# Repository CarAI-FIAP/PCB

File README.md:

# PCB
Placa em PCB para centralizar as conexões. Projeto em KiCAD

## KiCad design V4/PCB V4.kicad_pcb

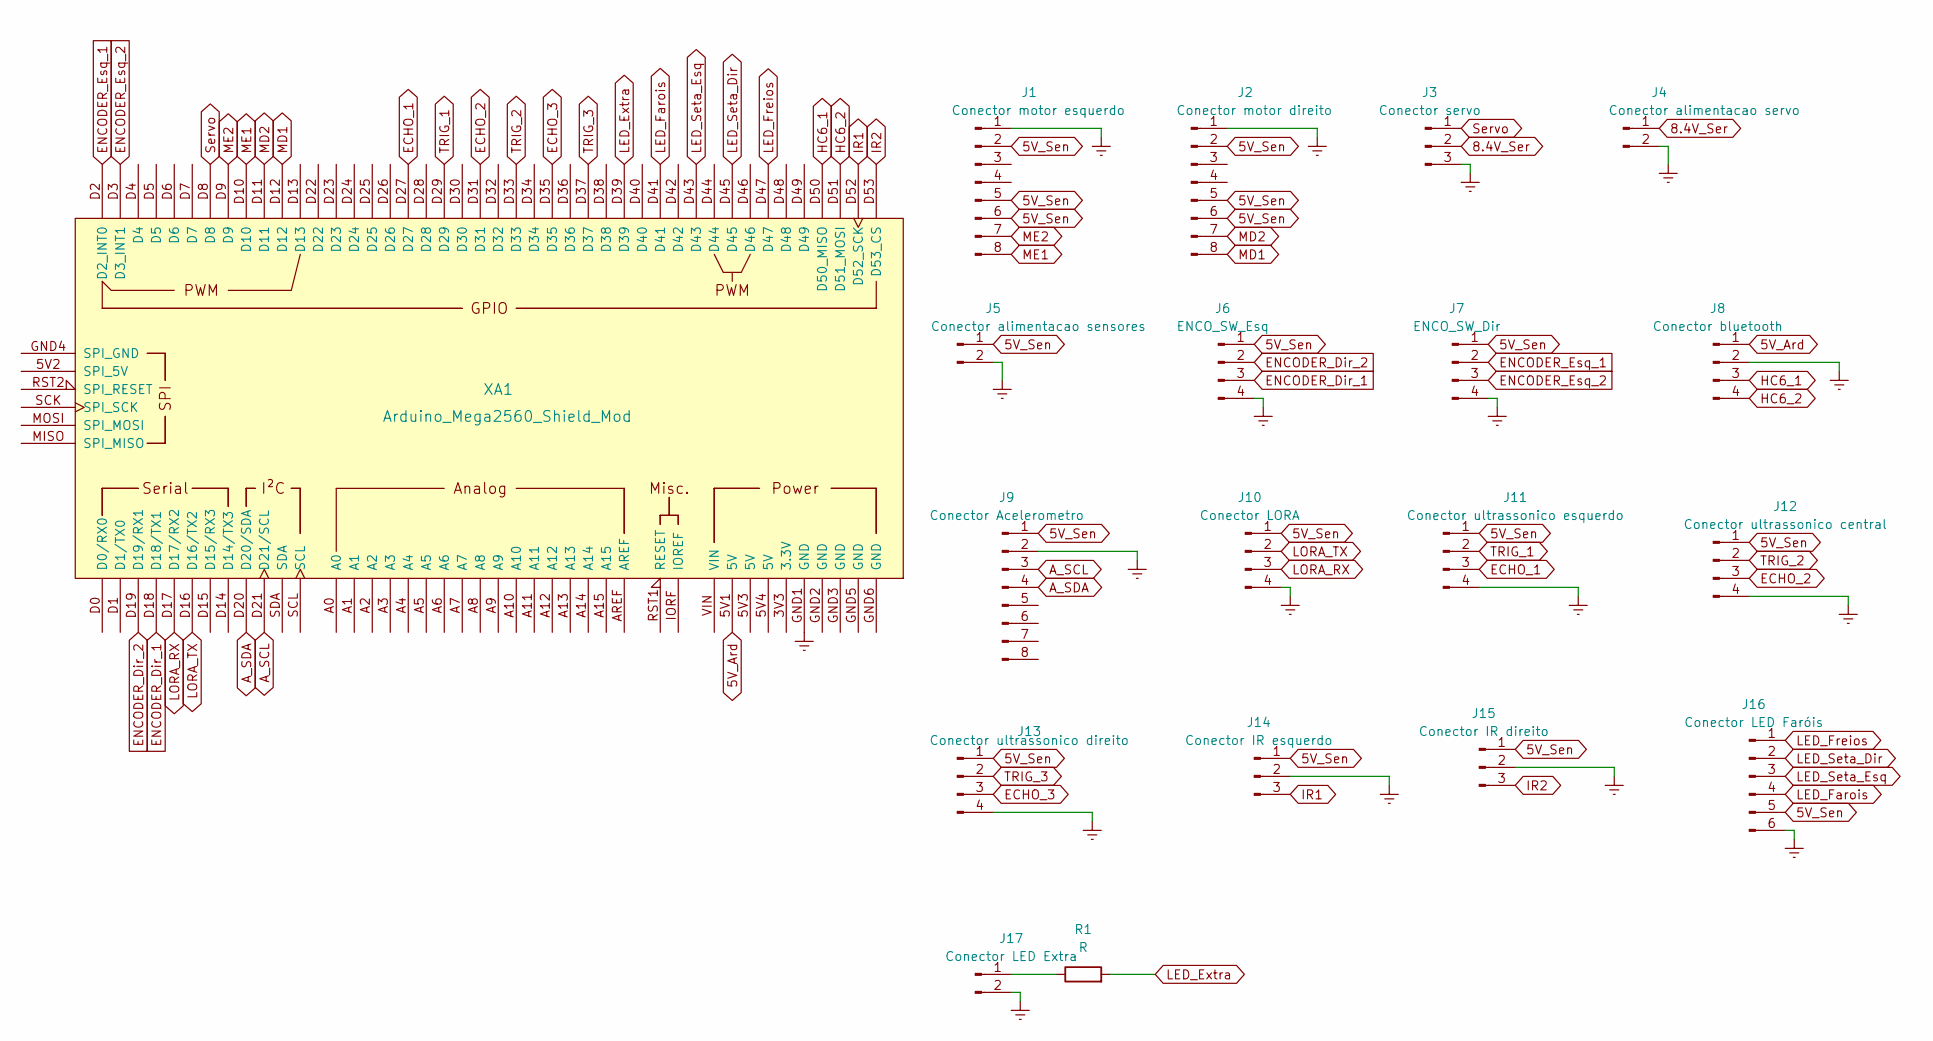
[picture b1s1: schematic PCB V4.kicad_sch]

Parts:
J1: Conector motor esquerdo; PinSocket_2x04_P2.54mm_Vertical
J2: Conector motor direito; PinSocket_2x04_P2.54mm_Vertical
J3: Conector servo; TerminalBlock_Phoenix_MKDS-1,5-3_1x03_P5.00mm_Horizontal
J4: Conector alimentacao servo; TerminalBlock_Phoenix_MKDS-1,5-2_1x02_P5.00mm_Horizontal
J5: Conector alimentacao sensores; TerminalBlock_Phoenix_MKDS-1,5-2_1x02_P5.00mm_Horizontal
J6: ENCO_SW_Esq; TerminalBlock_Phoenix_MKDS-1,5-4_1x04_P5.00mm_Horizontal
J7: ENCO_SW_Dir; TerminalBlock_Phoenix_MKDS-1,5-4_1x04_P5.00mm_Horizontal
J8: Conector bluetooth; PinSocket_1x04_P2.54mm_Vertical
J9: Conector Acelerometro; PinSocket_1x08_P2.54mm_Vertical
J10: Conector LORA; JST_XH_B4B-XH-A_1x04_P2.50mm_Vertical
J11: Conector ultrassonico esquerdo; JST_XH_B4B-XH-A_1x04_P2.50mm_Vertical
J12: Conector ultrassonico central; JST_XH_B4B-XH-A_1x04_P2.50mm_Vertical
J13: Conector ultrassonico direito; JST_XH_B4B-XH-A_1x04_P2.50mm_Vertical
J14: Conector IR esquerdo; JST_XH_B3B-XH-A_1x03_P2.50mm_Vertical
J15: Conector IR direito; JST_XH_B3B-XH-A_1x03_P2.50mm_Vertical
J16: Conector LED Faróis; TerminalBlock_Phoenix_MKDS-1,5-6_1x06_P5.00mm_Horizontal
J17: Conector LED Extra; JST_XH_B2B-XH-A_1x02_P2.50mm_Vertical
R1: R; R_Axial_DIN0207_L6.3mm_D2.5mm_P10.16mm_Horizontal
XA1: Arduino_Mega2560_Shield_Mod; Arduino_Mega2560_R3_Shield_No_Holes

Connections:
5V_Ard: J8.1, XA1.5V1 (5V)
5V_Sen: J1.2, J1.5, J1.6, J2.2, J2.5, J2.6, J5.1, J6.1, J7.1, J9.1, J10.1, J11.1, J12.1, J13.1, J14.1, J15.1, J16.5
8.4V_Ser: J3.2, J4.1
A_SCL: J9.3, XA1.D21 (D21/SCL)
A_SDA: J9.4, XA1.D20 (D20/SDA)
ECHO_1: J11.3, XA1.D27
ECHO_2: J12.3, XA1.D31
ECHO_3: J13.3, XA1.D35
ENCODER_Dir_1: J6.3, XA1.D18 (D18/TX1)
ENCODER_Dir_2: J6.2, XA1.D19 (D19/RX1)
ENCODER_Esq_1: J7.2, XA1.D2 (D2_INT0)
ENCODER_Esq_2: J7.3, XA1.D3 (D3_INT1)
Earth: J1.1, J2.1, J3.3, J4.2, J5.2, J6.4, J7.4, J8.2, J9.2, J10.4, J11.4, J12.4, J13.4, J14.2, J15.2, J16.6, J17.2, XA1.GND1 (GND)
HC6_1: J8.3, XA1.D50 (D50_MISO)
HC6_2: J8.4, XA1.D51 (D51_MOSI)
IR1: J14.3, XA1.D52 (D52_SCK)
IR2: J15.3, XA1.D53 (D53_CS)
LED_Extra: R1.2, XA1.D39
LED_Farois: J16.4, XA1.D41
LED_Freios: J16.1, XA1.D47
LED_Seta_Dir: J16.2, XA1.D45
LED_Seta_Esq: J16.3, XA1.D43
LORA_RX: J10.3, XA1.D17 (D17/RX2)
LORA_TX: J10.2, XA1.D16 (D16/TX2)
MD1: J2.8, XA1.D12
MD2: J2.7, XA1.D11
ME1: J1.8, XA1.D10
ME2: J1.7, XA1.D9
unnamed: J17.1, R1.1
Servo: J3.1, XA1.D8
TRIG_1: J11.2, XA1.D29
TRIG_2: J12.2, XA1.D33
TRIG_3: J13.2, XA1.D37

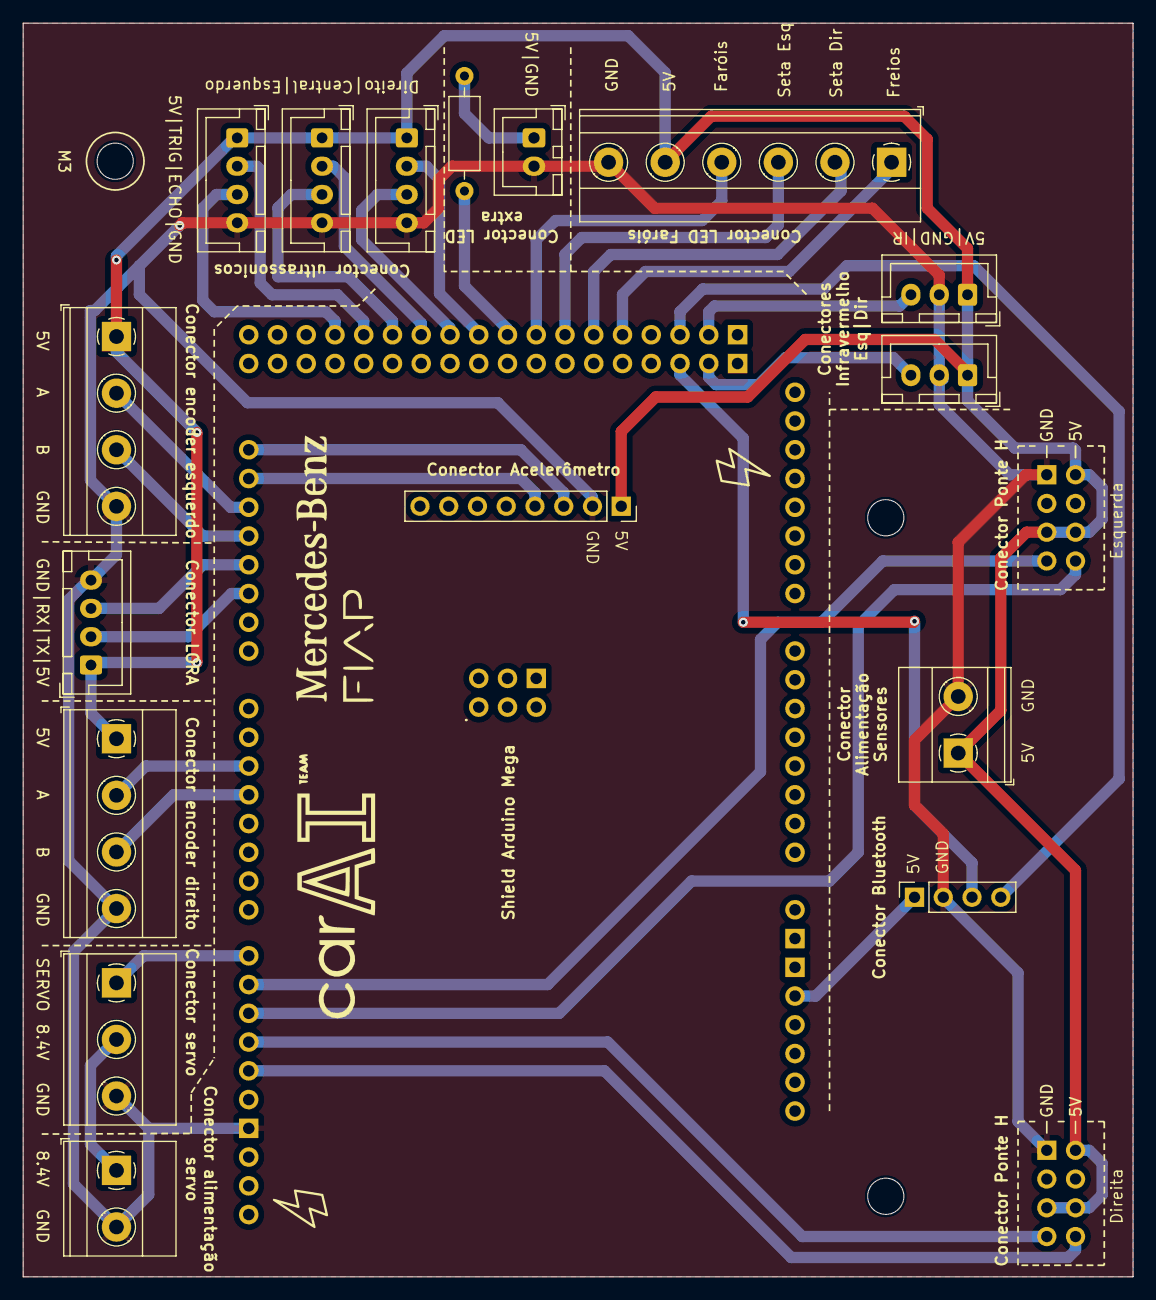
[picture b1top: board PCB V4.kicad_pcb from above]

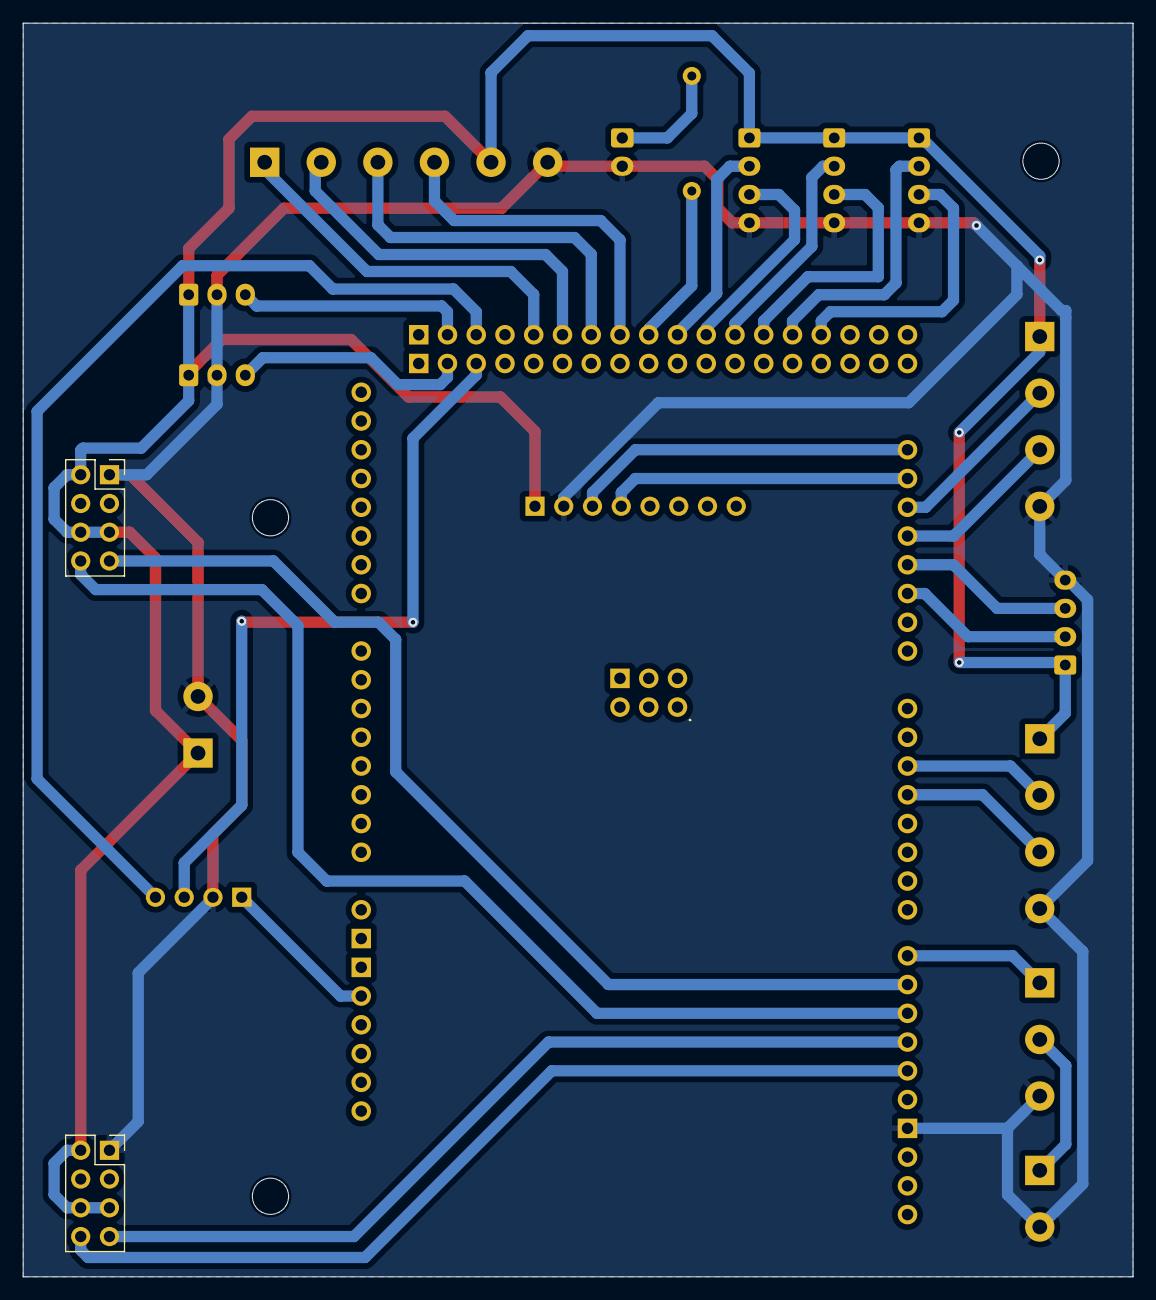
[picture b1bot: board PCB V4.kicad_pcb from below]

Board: 2 copper layers, 98.0 x 110.7 mm, 19 parts (2 on the bottom side), 33 nets.

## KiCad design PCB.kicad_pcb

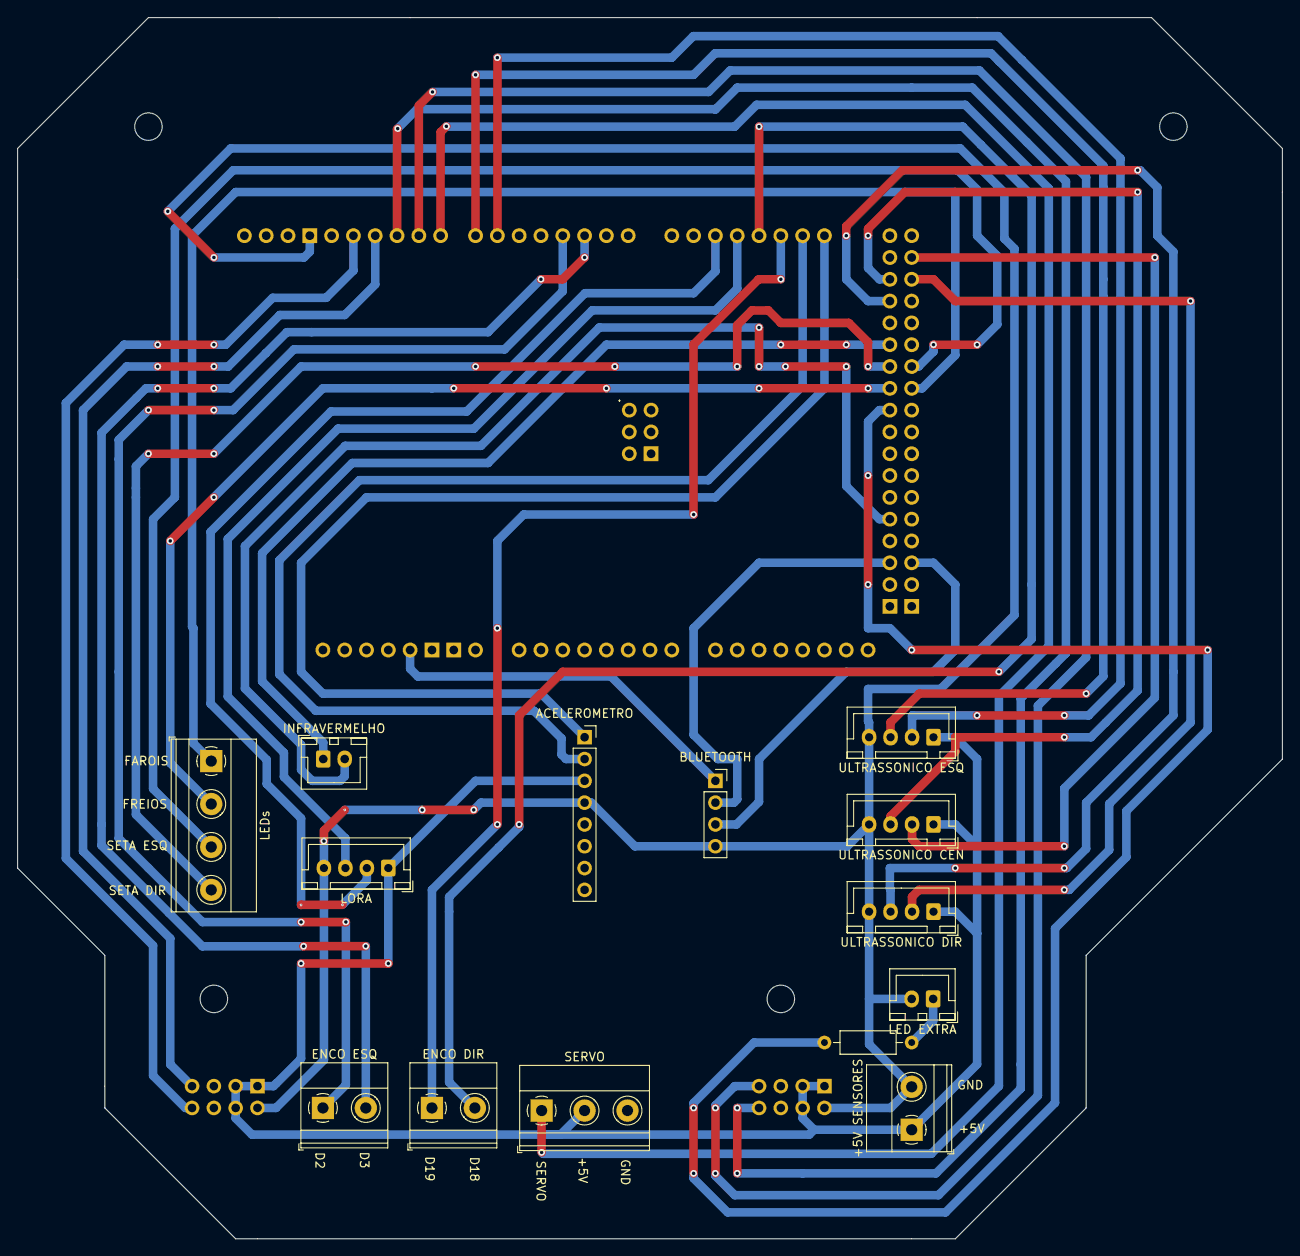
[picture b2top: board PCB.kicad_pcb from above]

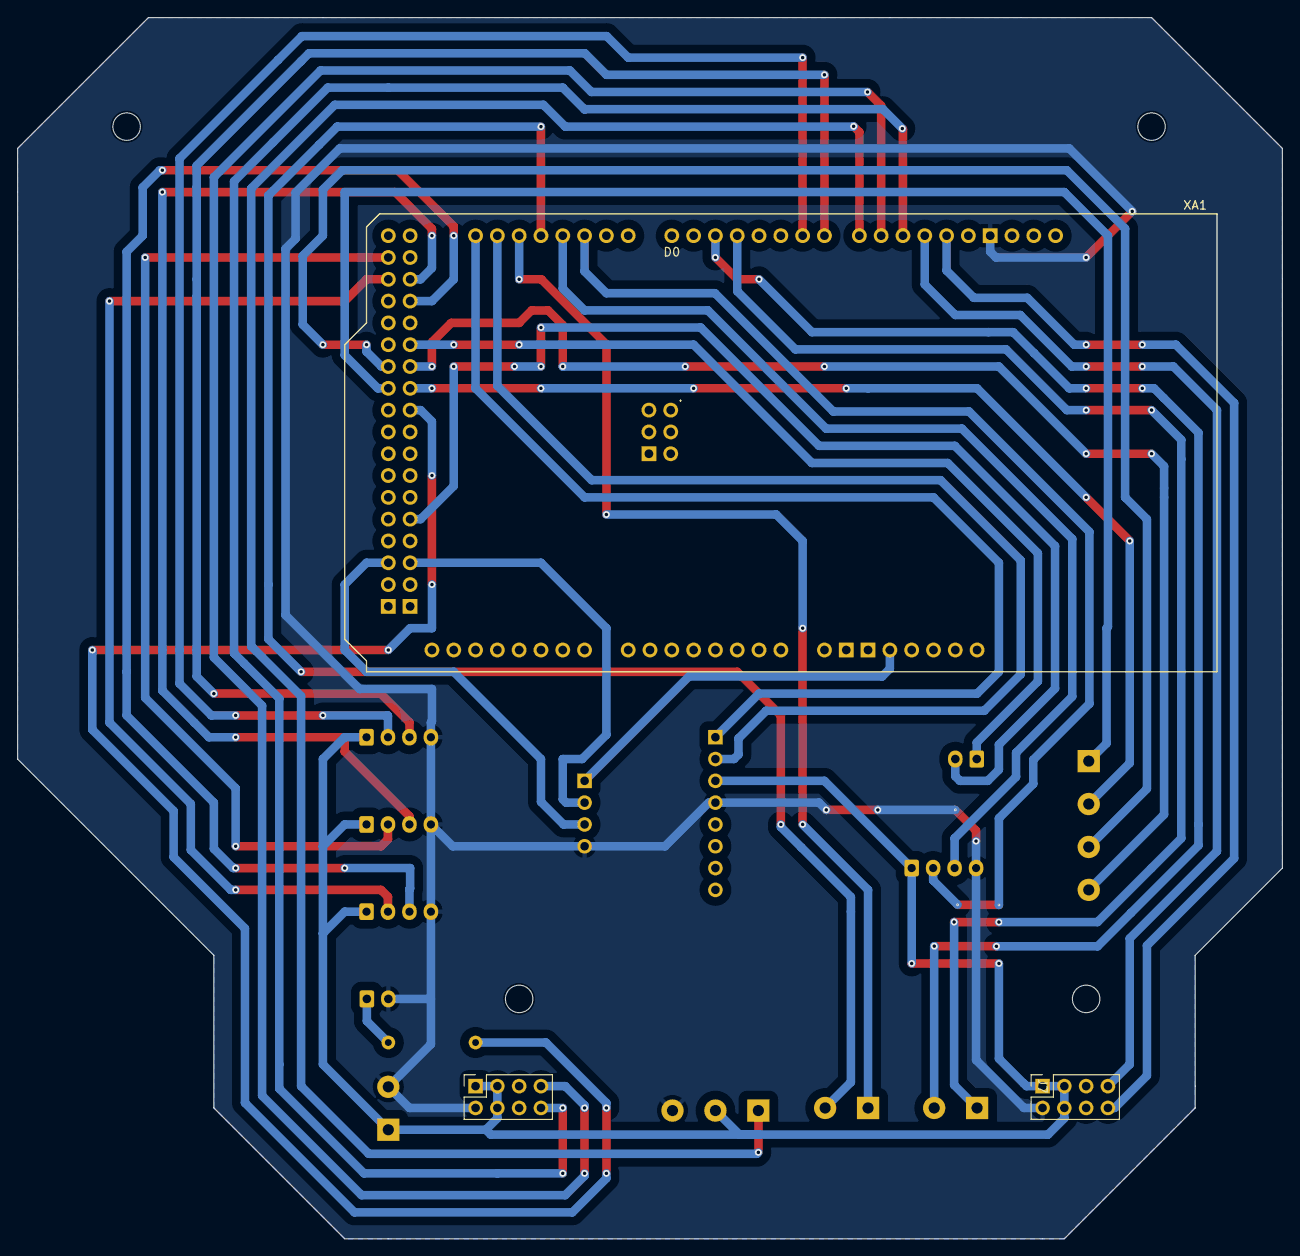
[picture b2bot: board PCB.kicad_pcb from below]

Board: 2 copper layers, 147.3 x 142.2 mm, 17 parts (2 on the bottom side), 32 nets.

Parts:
+5V SENSORES: Conector alimentacao sensores; TerminalBlock_Phoenix_MKDS-1,5-2_1x02_P5.00mm_Horizontal
ACELEROMETRO: Conector Acelerometro; PinSocket_1x08_P2.54mm_Vertical
BLUETOOTH: Conector bluetooth; PinSocket_1x04_P2.54mm_Vertical
ENCO DIR: ENCO_SW_Dir; TerminalBlock_Phoenix_MKDS-1,5-2_1x02_P5.00mm_Horizontal
ENCO ESQ: ENCO_SW_Esq; TerminalBlock_Phoenix_MKDS-1,5-2_1x02_P5.00mm_Horizontal
INFRAVERMELHO: Conector IR; JST_XH_B2B-XH-A_1x02_P2.50mm_Vertical
J7: PONTA H 1; PinSocket_2x04_P2.54mm_Vertical
LED EXTRA: Conector LED Extra; JST_XH_B2B-XH-A_1x02_P2.50mm_Vertical
LEDs: LEDs; TerminalBlock_Phoenix_MKDS-1,5-4_1x04_P5.00mm_Horizontal
LORA: Conector LORA; JST_XH_B4B-XH-A_1x04_P2.50mm_Vertical
PONTE H 2: Conector motor esquerdo; PinSocket_2x04_P2.54mm_Vertical
R1: R; R_Axial_DIN0207_L6.3mm_D2.5mm_P10.16mm_Horizontal
SERVO: Conector servo; TerminalBlock_Phoenix_MKDS-1,5-3_1x03_P5.00mm_Horizontal
ULTRASSONICO CEN: Conector ultrassonico central; JST_XH_B4B-XH-A_1x04_P2.50mm_Vertical
ULTRASSONICO DIR: Conector ultrassonico direito; JST_XH_B4B-XH-A_1x04_P2.50mm_Vertical
ULTRASSONICO ESQ: Conector ultrassonico esquerdo; JST_XH_B4B-XH-A_1x04_P2.50mm_Vertical
XA1: Arduino_Mega2560_Shield_Mod; Arduino_Mega2560_R3_Shield_Sem_furo

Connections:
5V_Ard: BLUETOOTH.1, XA1.5V1 (5V)
5V_Sen: +5V SENSORES.1, ACELEROMETRO.3, J7.1, J7.3, J7.4, LORA.1, PONTE H 2.1, PONTE H 2.3, PONTE H 2.4, SERVO.2, ULTRASSONICO CEN.1, ULTRASSONICO DIR.1, ULTRASSONICO ESQ.1
A_SCL: ACELEROMETRO.1, XA1.D21 (D21/SCL)
A_SDA: ACELEROMETRO.2, XA1.D20 (D20/SDA)
ECHO_1: ULTRASSONICO ESQ.2, XA1.D6
ECHO_2: ULTRASSONICO CEN.2, XA1.D23
ECHO_3: ULTRASSONICO DIR.2, XA1.D25
Earth: +5V SENSORES.2, ACELEROMETRO.4, BLUETOOTH.4, J7.2, LED EXTRA.2, LORA.4, PONTE H 2.2, SERVO.3, ULTRASSONICO CEN.4, ULTRASSONICO DIR.4, ULTRASSONICO ESQ.4, XA1.GND1 (GND)
HC6_1: BLUETOOTH.2, XA1.D50 (D50_MISO)
HC6_2: BLUETOOTH.3, XA1.D51 (D51_MOSI)
IR1: INFRAVERMELHO.1, XA1.D30
IR2: INFRAVERMELHO.2, XA1.D46
LED_Extra: R1.2, XA1.D36
LORA_RX: LORA.3, XA1.D17 (D17/RX2)
LORA_TX: LORA.2, XA1.D16 (D16/TX2)
MD1: J7.8, XA1.D12
MD2: J7.7, XA1.D11
ME1: PONTE H 2.8, XA1.D10
ME2: PONTE H 2.7, XA1.D9
unnamed: ENCO ESQ.1, XA1.D3 (D3_INT1)
unnamed: ENCO ESQ.2, XA1.D2 (D2_INT0)
unnamed: ENCO DIR.1, XA1.D19 (D19/RX1)
unnamed: ENCO DIR.2, XA1.D18 (D18/TX1)
unnamed: LED EXTRA.1, R1.1
unnamed: LEDs.1, XA1.D35
unnamed: LEDs.2, XA1.D34
unnamed: LEDs.3, XA1.D33
unnamed: LEDs.4, XA1.D32
Servo: SERVO.1, XA1.D8
TRIG_1: ULTRASSONICO ESQ.3, XA1.D7
TRIG_2: ULTRASSONICO CEN.3, XA1.D24
TRIG_3: ULTRASSONICO DIR.3, XA1.D26

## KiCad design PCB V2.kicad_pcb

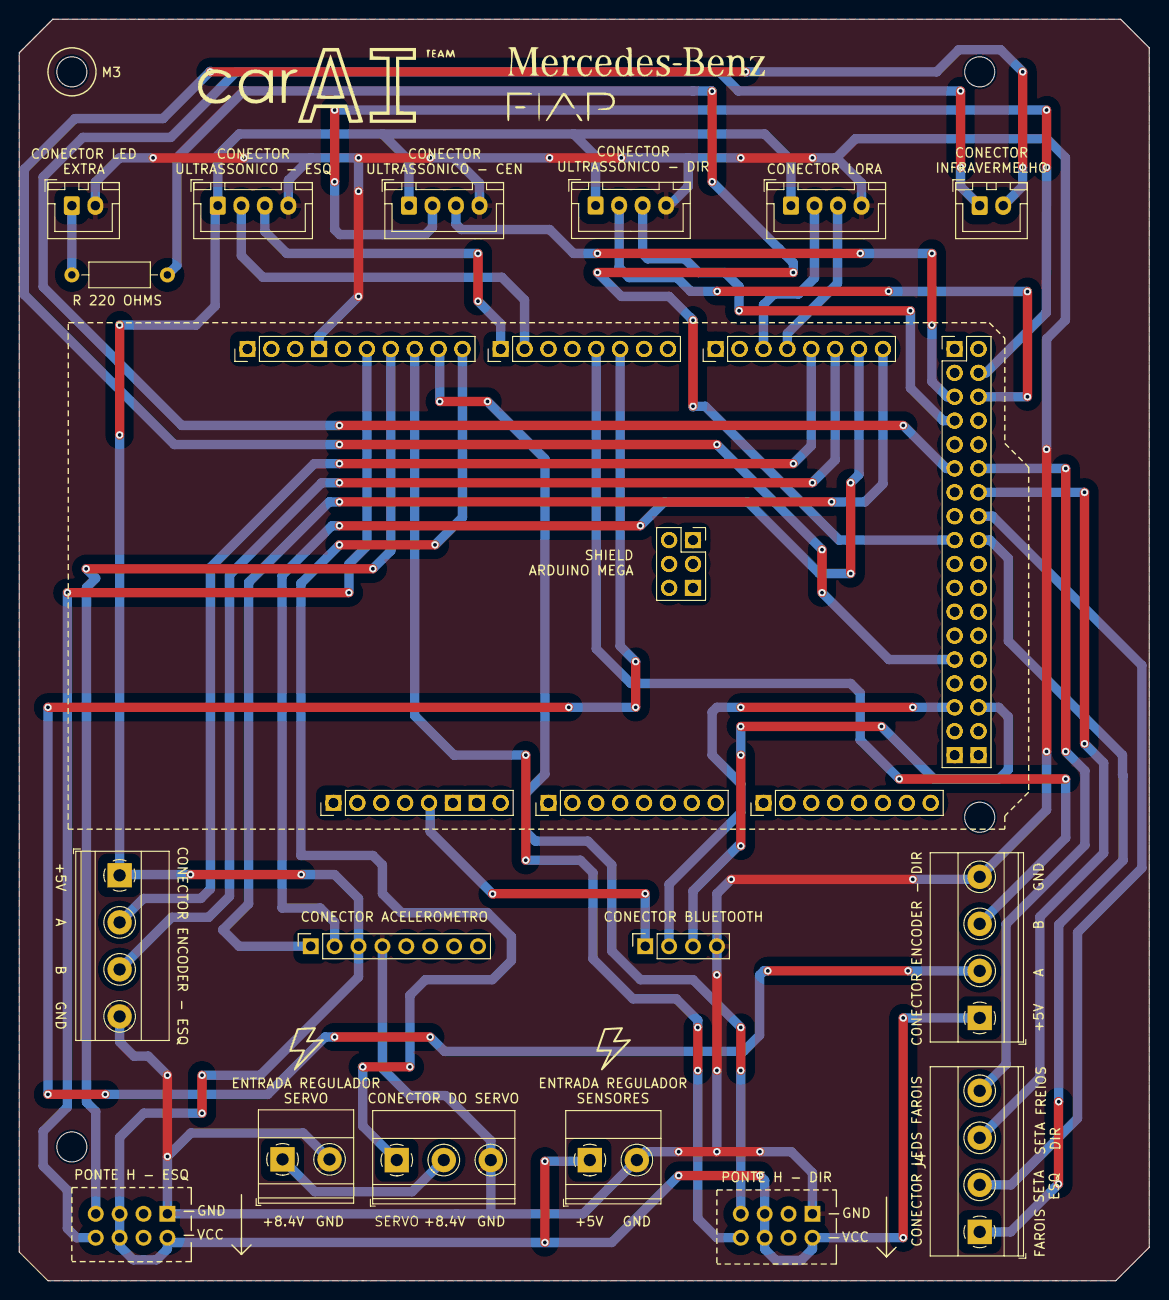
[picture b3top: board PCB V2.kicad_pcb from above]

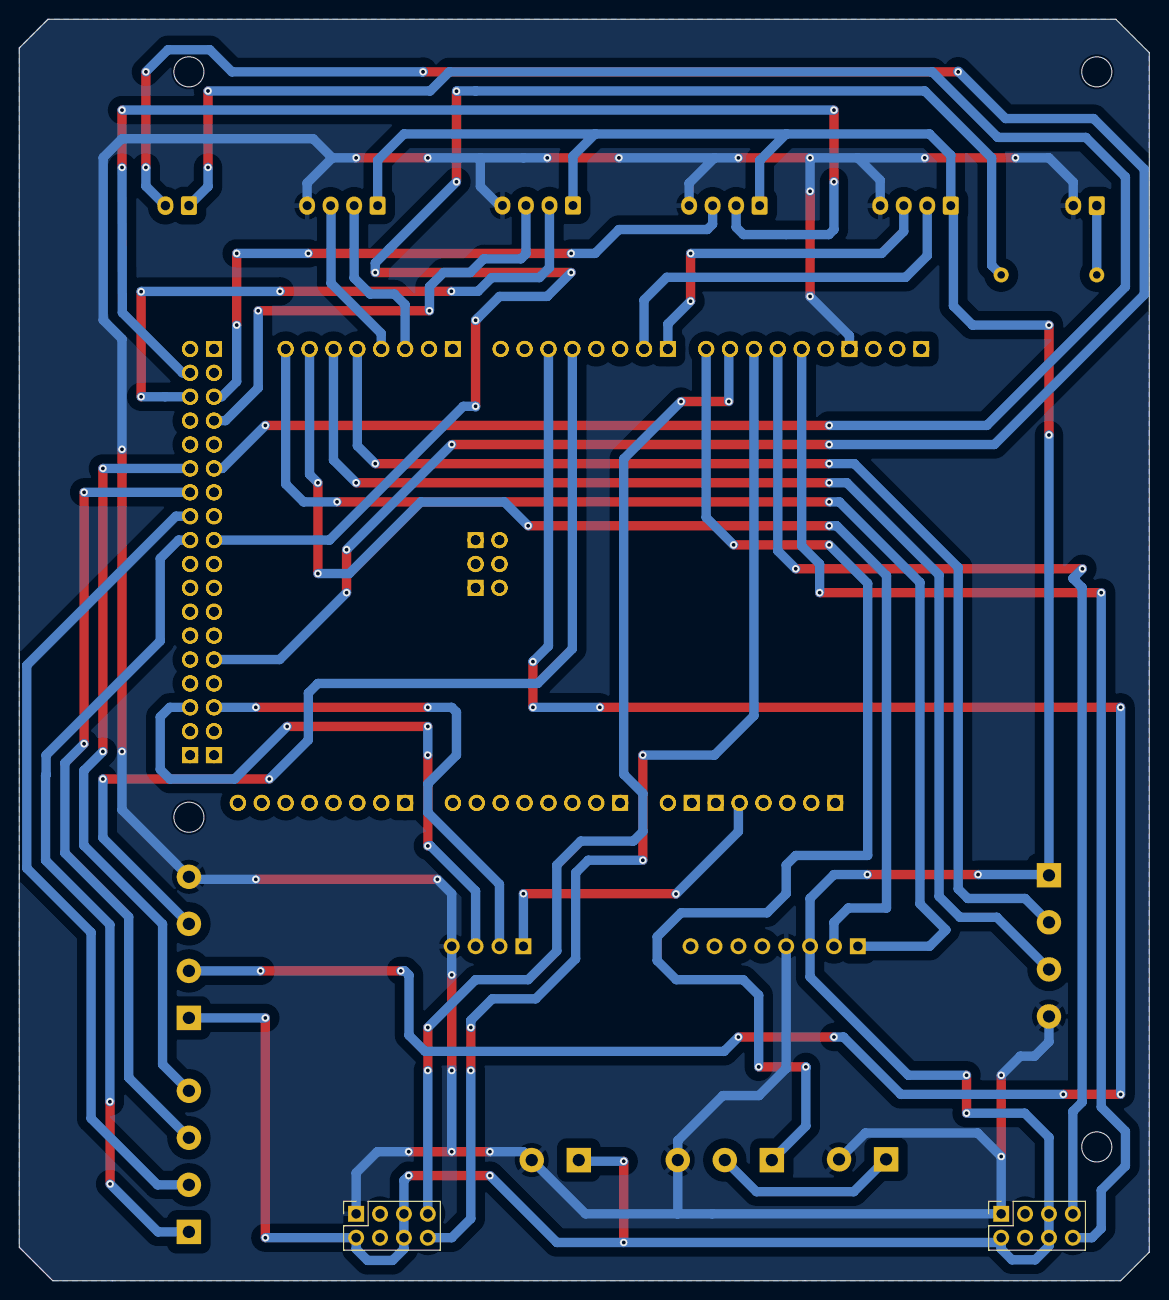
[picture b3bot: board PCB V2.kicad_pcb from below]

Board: 2 copper layers, 120.1 x 134.1 mm, 18 parts (2 on the bottom side), 33 nets.

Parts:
J1: Conector IR; JST_XH_B2B-XH-A_1x02_P2.50mm_Vertical
J2: Conector bluetooth; PinSocket_1x04_P2.54mm_Vertical
J3: Conector Acelerometro; PinSocket_1x08_P2.54mm_Vertical
J4: LEDs; TerminalBlock_Phoenix_MKDS-1,5-4_1x04_P5.00mm_Horizontal
J5: Conector servo; TerminalBlock_Phoenix_MKDS-1,5-3_1x03_P5.00mm_Horizontal
J6: Conector alimentacao servo; TerminalBlock_Phoenix_MKDS-1,5-2_1x02_P5.00mm_Horizontal
J7: Conector motor direito; PinSocket_2x04_P2.54mm_Vertical
J8: Conector motor esquerdo; PinSocket_2x04_P2.54mm_Vertical
J9: Conector alimentacao sensores; TerminalBlock_Phoenix_MKDS-1,5-2_1x02_P5.00mm_Horizontal
J10: Conector ultrassonico esquerdo; JST_XH_B4B-XH-A_1x04_P2.50mm_Vertical
J11: Conector ultrassonico central; JST_XH_B4B-XH-A_1x04_P2.50mm_Vertical
J12: Conector ultrassonico direito; JST_XH_B4B-XH-A_1x04_P2.50mm_Vertical
J13: Conector LED Extra; JST_XH_B2B-XH-A_1x02_P2.50mm_Vertical
J14: Conector LORA; JST_XH_B4B-XH-A_1x04_P2.50mm_Vertical
J15: ENCO_SW_Esq; TerminalBlock_Phoenix_MKDS-1,5-4_1x04_P5.00mm_Horizontal
J16: ENCO_SW_Dir; TerminalBlock_Phoenix_MKDS-1,5-4_1x04_P5.00mm_Horizontal
R1: R; R_Axial_DIN0207_L6.3mm_D2.5mm_P10.16mm_Horizontal
XA1: Arduino_Mega2560_Shield_Mod; Arduino_Mega2560_R3_Shield_Sem_furo

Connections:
5V_Ard: J2.1, XA1.5V1 (5V)
5V_Sen: J3.3, J7.2, J7.5, J7.6, J8.2, J8.5, J8.6, J9.1, J10.1, J11.1, J12.1, J14.1, J15.1, J16.1
8.4V_Ser: J5.2, J6.1
A_SCL: J3.1, XA1.D21 (D21/SCL)
A_SDA: J3.2, XA1.D20 (D20/SDA)
ECHO_1: J10.2, XA1.D6
ECHO_2: J11.2, XA1.D23
ECHO_3: J12.2, XA1.D25
ENCODER_Dir_1: J15.2, XA1.D18 (D18/TX1)
ENCODER_Dir_2: J15.3, XA1.D19 (D19/RX1)
ENCODER_Esq_1: J16.2, XA1.D2 (D2_INT0)
ENCODER_Esq_2: J16.3, XA1.D3 (D3_INT1)
Earth: J2.4, J3.4, J5.3, J6.2, J7.1, J8.1, J9.2, J10.4, J11.4, J12.4, J13.2, J14.4, J15.4, J16.4, XA1.GND1 (GND)
HC6_1: J2.2, XA1.D50 (D50_MISO)
HC6_2: J2.3, XA1.D51 (D51_MOSI)
IR1: J1.1, XA1.D30
IR2: J1.2, XA1.D46
LED_Extra: R1.2, XA1.D36
LED_Farois: J4.1, XA1.D37
LED_Freios: J4.4, XA1.D31
LED_Seta_Dir: J4.3, XA1.D33
LED_Seta_Esq: J4.2, XA1.D35
LORA_RX: J14.3, XA1.D17 (D17/RX2)
LORA_TX: J14.2, XA1.D16 (D16/TX2)
MD1: J7.8, XA1.D12
MD2: J7.7, XA1.D11
ME1: J8.8, XA1.D10
ME2: J8.7, XA1.D9
unnamed: J13.1, R1.1
Servo: J5.1, XA1.D8
TRIG_1: J10.3, XA1.D7
TRIG_2: J11.3, XA1.D24
TRIG_3: J12.3, XA1.D26

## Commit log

2023-09-06 feat: pcb layout e conexoes no esquematico
2023-09-06 feat: criacao do pcb
2023-09-07 feat: inicio da nova versao da pcb
2023-09-08 feat: finalizacao da versao 2 da pcb
2023-09-08 fix: criacao de pasta "renders"
2023-09-08 fix: adicao de uma foto no README
2023-09-08 fix: adicao de imagens ao README
2023-09-08 fix: ajuste de imagens no README
2023-09-08 fix: mudanca esquematico leds farois
2023-09-09 fix: adição da entrada 8.4V do servo e outros
2023-09-09 feat: criacao da versao 3 da pcb e organizacao
2023-09-09 feat: criação dos arquivos de manufatura
2023-09-14 feat: criação do V4 com corte quadrado
2023-09-14 fix: compactação dos arquivos de manufatura
